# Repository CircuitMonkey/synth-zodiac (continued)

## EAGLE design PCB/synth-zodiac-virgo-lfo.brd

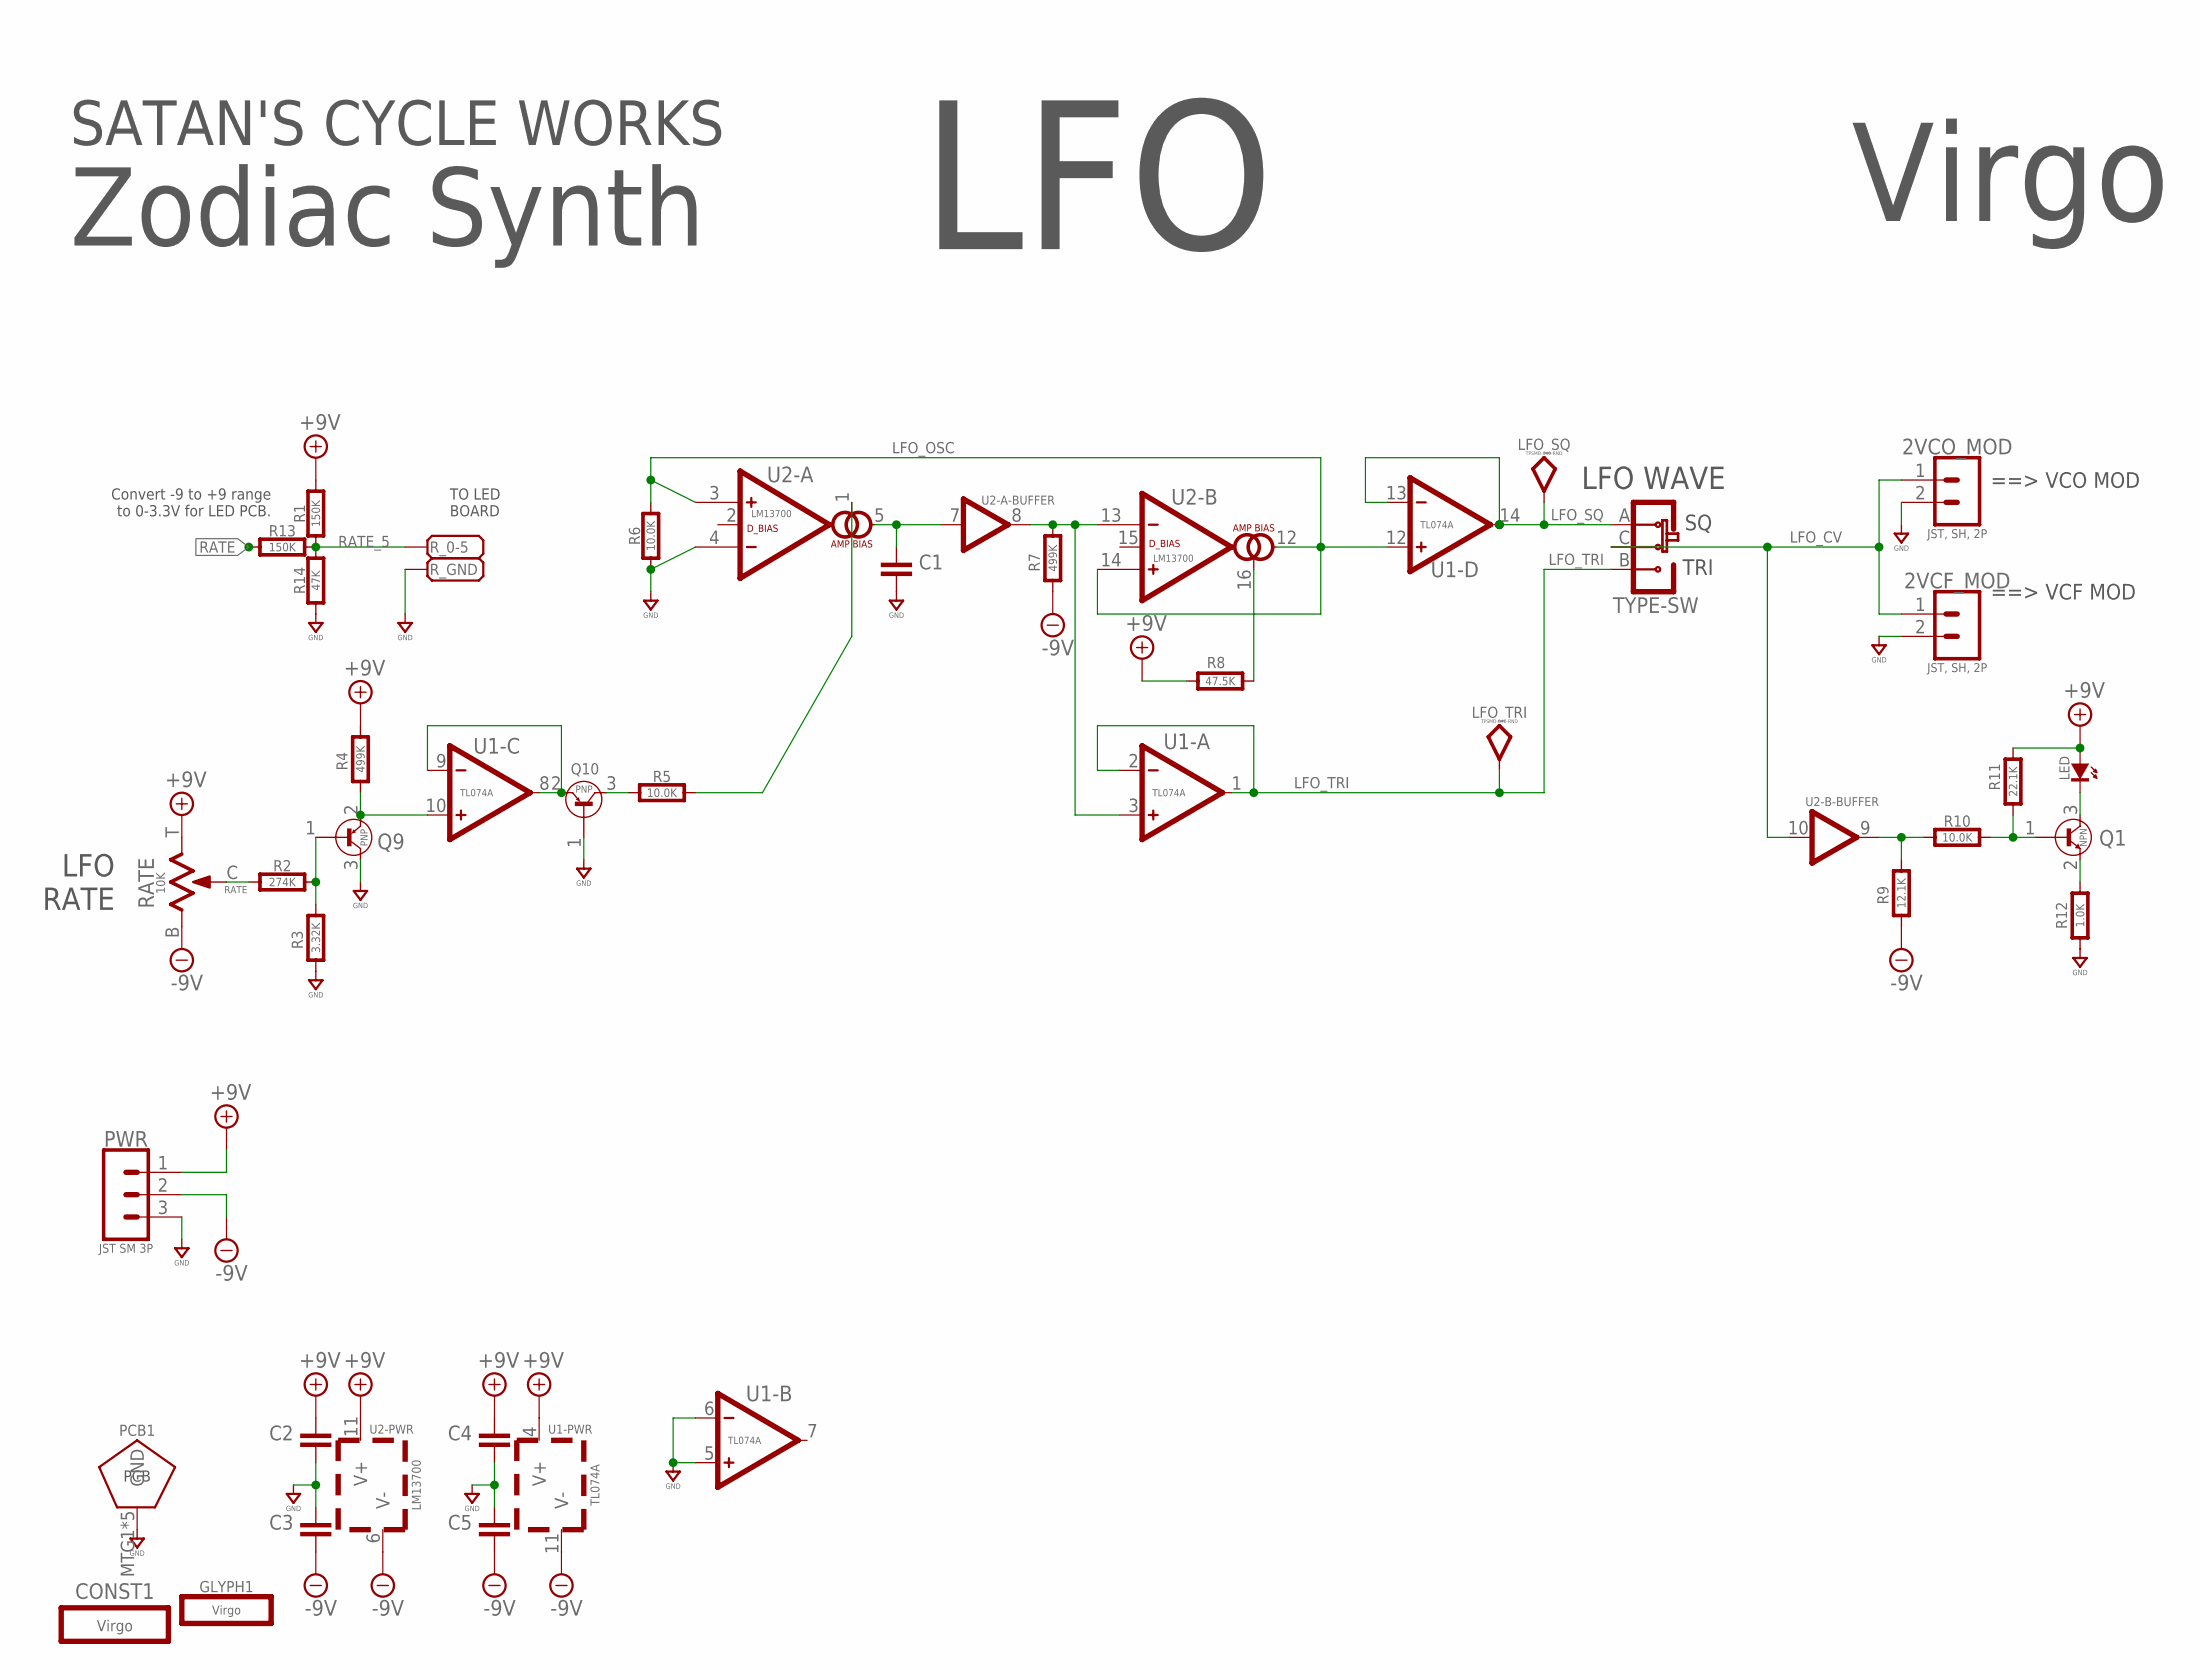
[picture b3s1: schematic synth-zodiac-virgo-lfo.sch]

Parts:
2VCF_MOD, 2VCO_MOD: JST, SH, 2P; BM02B-SRSS-TB
C1, C2, C3, C4, C5: 0.1uF; 0603-CAP
CONST1: Virgo; VIRGO-CONST
GLYPH1: Virgo; VIRGO-GLYPH
LED: BLU; SMD_0603
LFO_SQ: TPSMD-040-RND; SMD-040MIL-RND
LFO_TRI: TPSMD-040-RND; SMD-040MIL-RND
PCB1: PCB FAB; PENTAGON-40MM-RAD
PWR: JST SM 3P; BM03B-SRSS-TB
Q1: NPN; SOT-23
Q9, Q10: PNP; SOT-23
R1, R13: 150K; 0603-RES
R2: 274K; 0603-RES
R3: 3.32K; 0603-RES
R4, R7: 499K; 0603-RES
R5, R6, R10: 10.0K; 0603-RES
R8: 47.5K; 0603-RES
R9: 12.1K; 0603-RES
R11: 22.1K; 0603-RES
R12: 1.0K; 0603-RES
R14: 47K; 0603-RES
RATE: 10K; POT-RV9110
R_0-5: PADSMD-070X070; SMD-070MIL
R_GND: PADSMD-070X070; SMD-070MIL
TYPE: SLIDE-SPDT-MNTSS-12-F45-TH-PCB-2; SS-12-F45-PNL-SMT-2
U1: TL074A; SOP14
U2: LM13700; SO16

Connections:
+9V: C2.1, C4.1, LED.A, PWR.1, R1.2, R4.1, R8.2, R11.1, RATE.T (3), U1.4 (V+), U2.11 (V+)
-9V: C3.2, C5.2, PWR.2, R7.2, R9.2, RATE.B (1), U1.11 (V-), U2.6 (V-)
GND: 2VCF_MOD.2, 2VCO_MOD.2, C1.2, C2.2, C3.1, C4.2, C5.1, PCB1.MTG1, PCB1.MTG2, PCB1.MTG3, PCB1.MTG4, PCB1.MTG5, PWR.3, Q9.3 (COLLECTOR), Q10.1 (BASE), R3.2, R6.1, R12.2, R14.1, R_GND.1, U1.5 (+), U1.6 (-), U2.4 (-)
LFO_CV: 2VCF_MOD.1, 2VCO_MOD.1, TYPE.C, U2.10 (IN)
LFO_OSC: R6.2, U1.12 (+), U2.3 (+), U2.12 (OUT), U2.14 (+)
LFO_SQ: LFO_SQ.TP, TYPE.A, U1.13 (-), U1.14 (OUT)
LFO_TRI: LFO_TRI.TP, TYPE.B, U1.1 (OUT), U1.2 (-)
unnamed: Q9.1 (BASE), R2.2, R3.1
unnamed: Q9.2 (EMITTER), R4.2, U1.10 (+)
unnamed: Q10.2 (EMITTER), U1.8 (OUT), U1.9 (-)
unnamed: Q10.3 (COLLECTOR), R5.1
unnamed: R5.2, U2.1 (AMP-BIAS)
unnamed: C1.1, U2.5 (OUT), U2.7 (IN)
unnamed: R7.1, U1.3 (+), U2.8 (OUT), U2.13 (-)
unnamed: R8.1, U2.16 (AMP-BIAS)
unnamed: Q1.1 (BASE), R10.2, R11.2
unnamed: Q1.2 (EMITTER), R12.1
unnamed: R9.1, R10.1, U2.9 (OUT)
unnamed: LED.K (C), Q1.3 (COLLECTOR)
RATE: R2.1, R13.1, RATE.C (2)
RATE_5: R1.1, R13.2, R14.2, R_0-5.1

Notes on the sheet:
LFO RATE
LFO WAVE
TRI
==> VCO MOD
==> VCF MOD
TO LED BOARD
Convert -9 to +9 range to 0-3.3V for LED PCB.
LFO
Zodiac Synth
Virgo
SATAN'S CYCLE WORKS

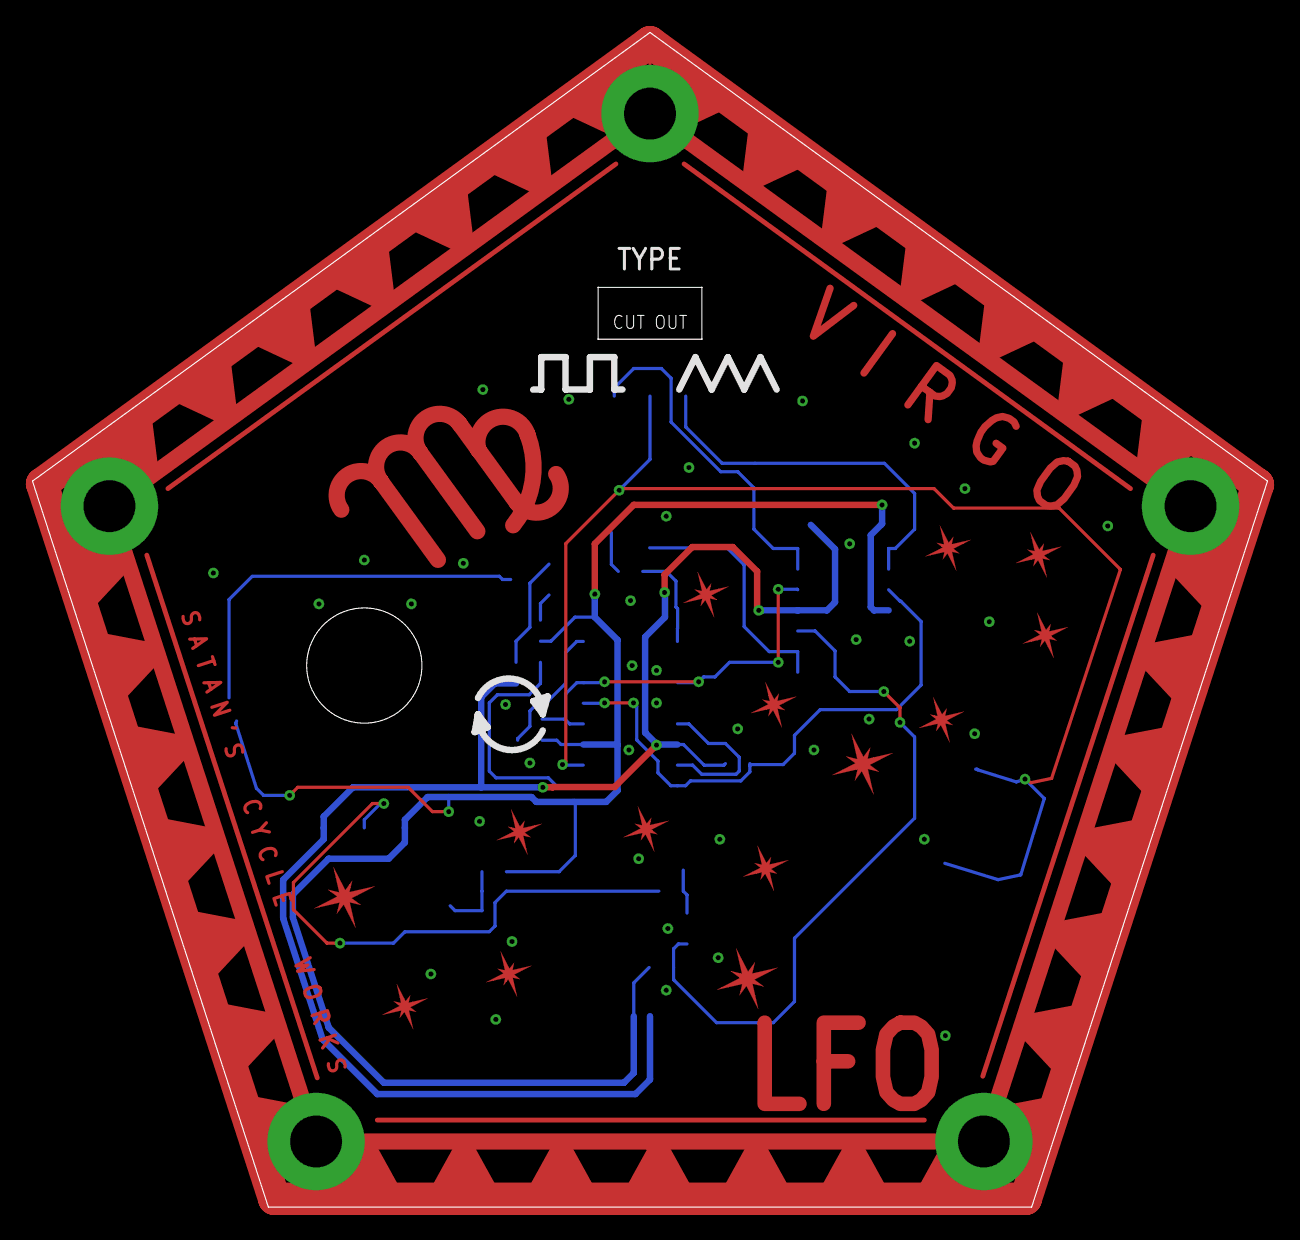
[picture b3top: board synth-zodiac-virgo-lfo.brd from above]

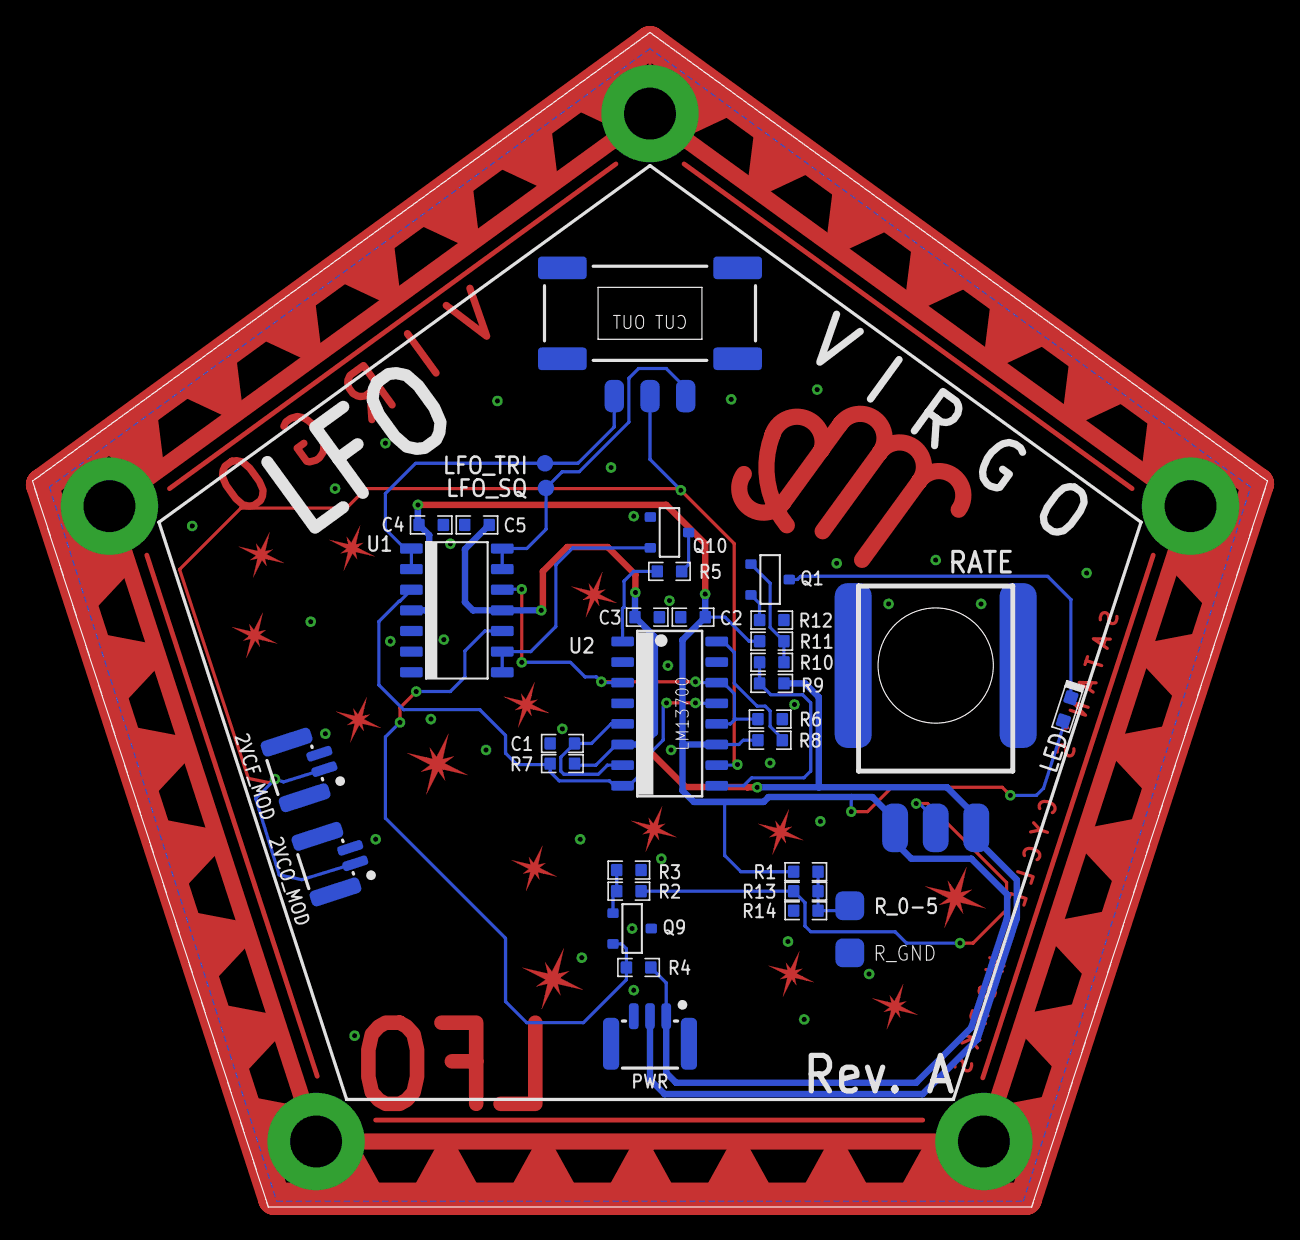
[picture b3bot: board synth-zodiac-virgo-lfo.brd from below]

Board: 2 copper layers, 76.1 x 72.3 mm, 37 parts (33 on the bottom side), 21 nets.

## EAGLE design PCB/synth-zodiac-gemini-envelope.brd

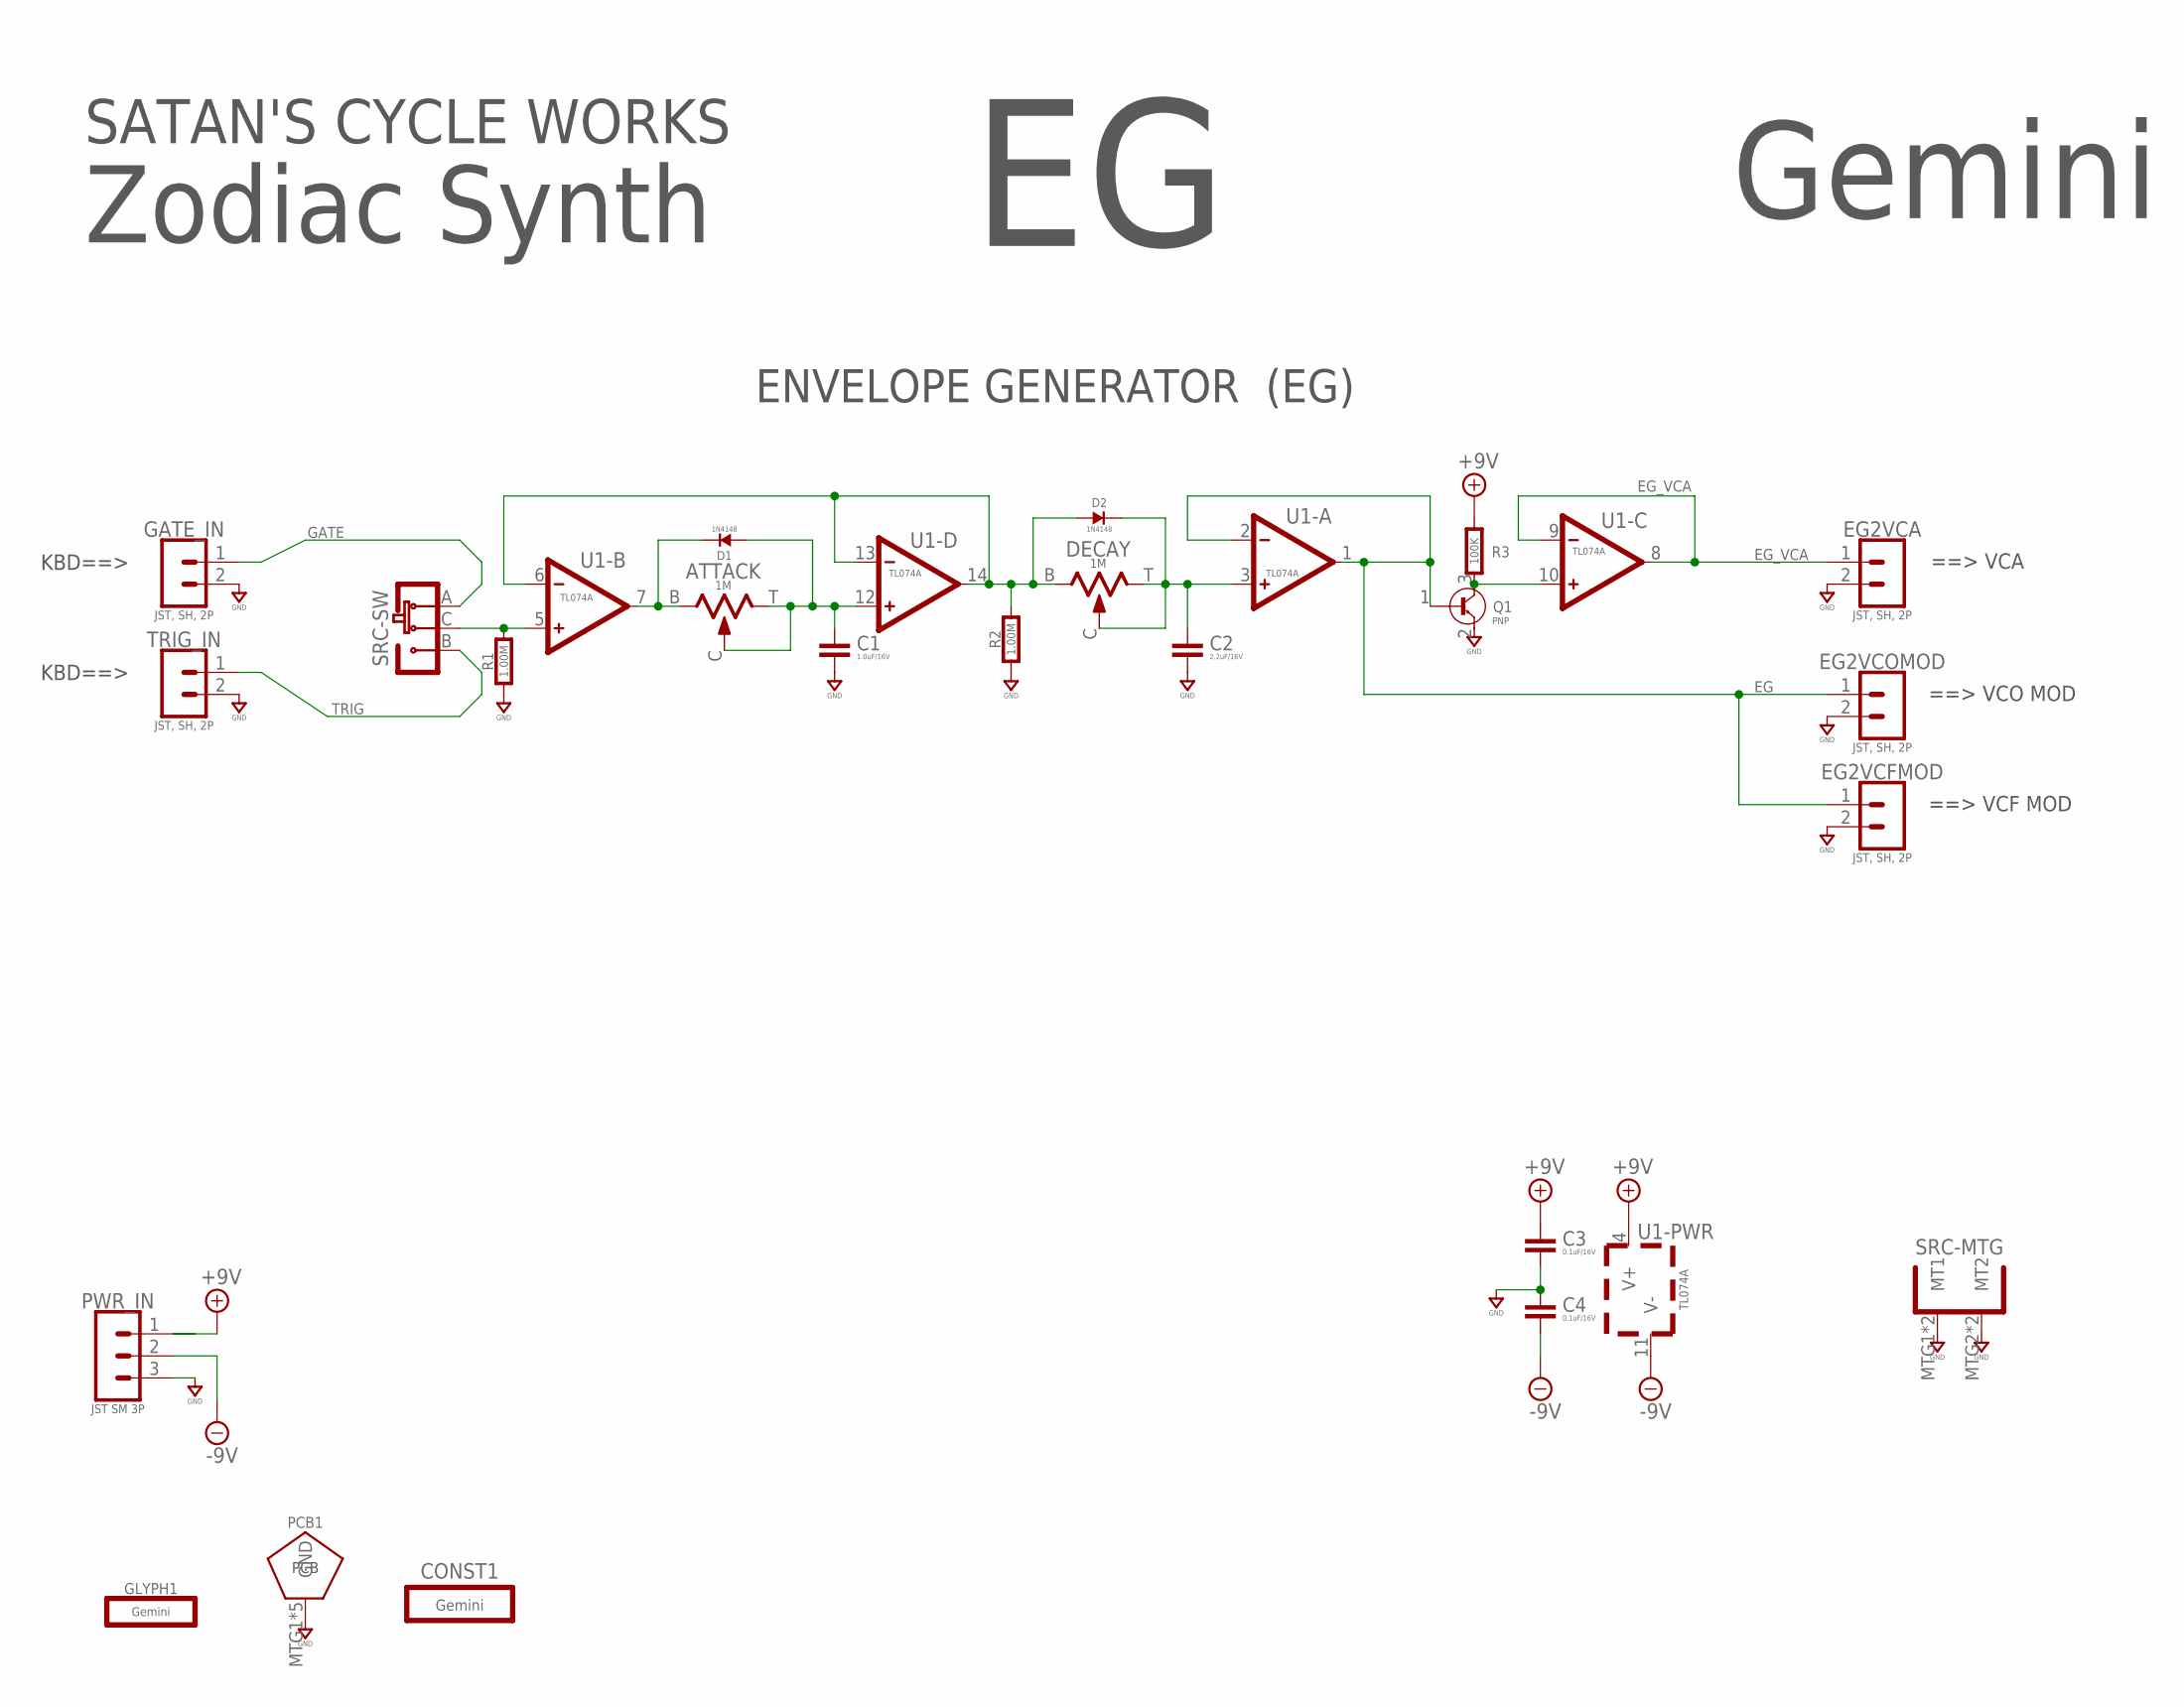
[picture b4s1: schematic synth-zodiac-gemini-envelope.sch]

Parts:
ATTACK: 1M; POT-RV9110
C1: 1.0uF/16V; 0603-CAP
C2: 2.2uF/16V; 0603-CAP
C3, C4: 0.1uF/16V; 0603-CAP
CONST1: Gemini; GEMINI-CONST
D1, D2: 1N4148; SOD-123
DECAY: 1M; POT-RV9110
EG2VCA, EG2VCFMOD, EG2VCOMOD: JST, SH, 2P; BM02B-SRSS-TB
GATE_IN: JST, SH, 2P; BM02B-SRSS-TB
GLYPH1: Gemini; GEMINI-GLYPH
PCB1: PCB FAB; PENTAGON-40MM-RAD
PWR_IN: JST SM 3P; BM03B-SRSS-TB
Q1: PNP; SOT-23
R1, R2: 1.00M; 0603-RES
R3: 100K; 0603-RES
SRC: SLIDE-SPDT-MNTSS-12-F45-TH-PCB-2; SS-12-F45-PNL-SMT-2
TRIG_IN: JST, SH, 2P; BM02B-SRSS-TB
U1: TL074A; SOP14

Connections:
+9V: C3.1, PWR_IN.1, R3.2, U1.4 (V+)
-9V: C4.2, PWR_IN.2, U1.11 (V-)
EG: EG2VCFMOD.1, EG2VCOMOD.1, Q1.1 (BASE), U1.1 (OUT), U1.2 (-)
EG_VCA: EG2VCA.1, U1.8 (OUT), U1.9 (-)
GATE: GATE_IN.1, SRC.A
GND: C1.2, C2.2, C3.2, C4.1, EG2VCA.2, EG2VCFMOD.2, EG2VCOMOD.2, GATE_IN.2, PCB1.MTG1, PCB1.MTG2, PCB1.MTG3, PCB1.MTG4, PCB1.MTG5, PWR_IN.3, Q1.2 (EMITTER), R1.1, R2.1, SRC.MTG1 (MT1), SRC.MTG2 (MT2), SRC.MTG3 (MT1), SRC.MTG4 (MT2), TRIG_IN.2
unnamed: R1.2, SRC.C, U1.5 (+)
unnamed: ATTACK.B (1), D1.K, U1.7 (OUT)
unnamed: ATTACK.C (2), ATTACK.T (3), C1.1, D1.A, U1.12 (+)
unnamed: C2.1, D2.K, DECAY.C (2), DECAY.T (3), U1.3 (+)
unnamed: D2.A, DECAY.B (1), R2.2, U1.6 (-), U1.13 (-), U1.14 (OUT)
unnamed: Q1.3 (COLLECTOR), R3.1, U1.10 (+)
TRIG: SRC.B, TRIG_IN.1

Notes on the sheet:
ENVELOPE GENERATOR (EG)
==> VCO MOD
==> VCA
==> VCF MOD
KBD==>
Zodiac Synth
Gemini
SATAN'S CYCLE WORKS

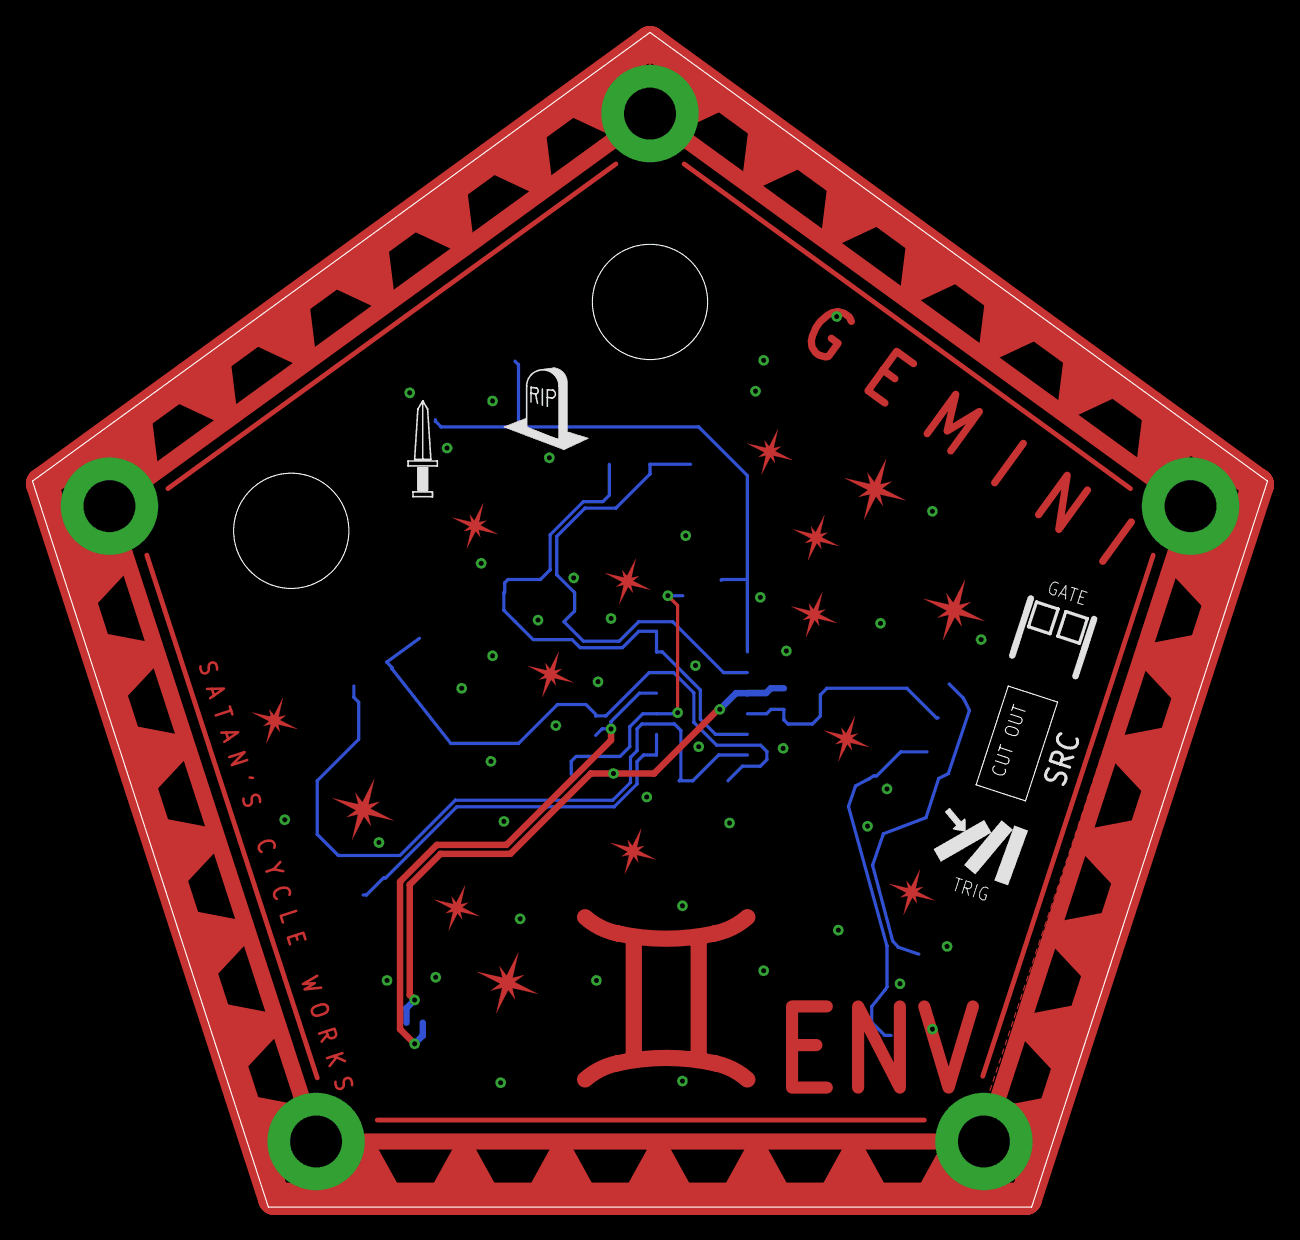
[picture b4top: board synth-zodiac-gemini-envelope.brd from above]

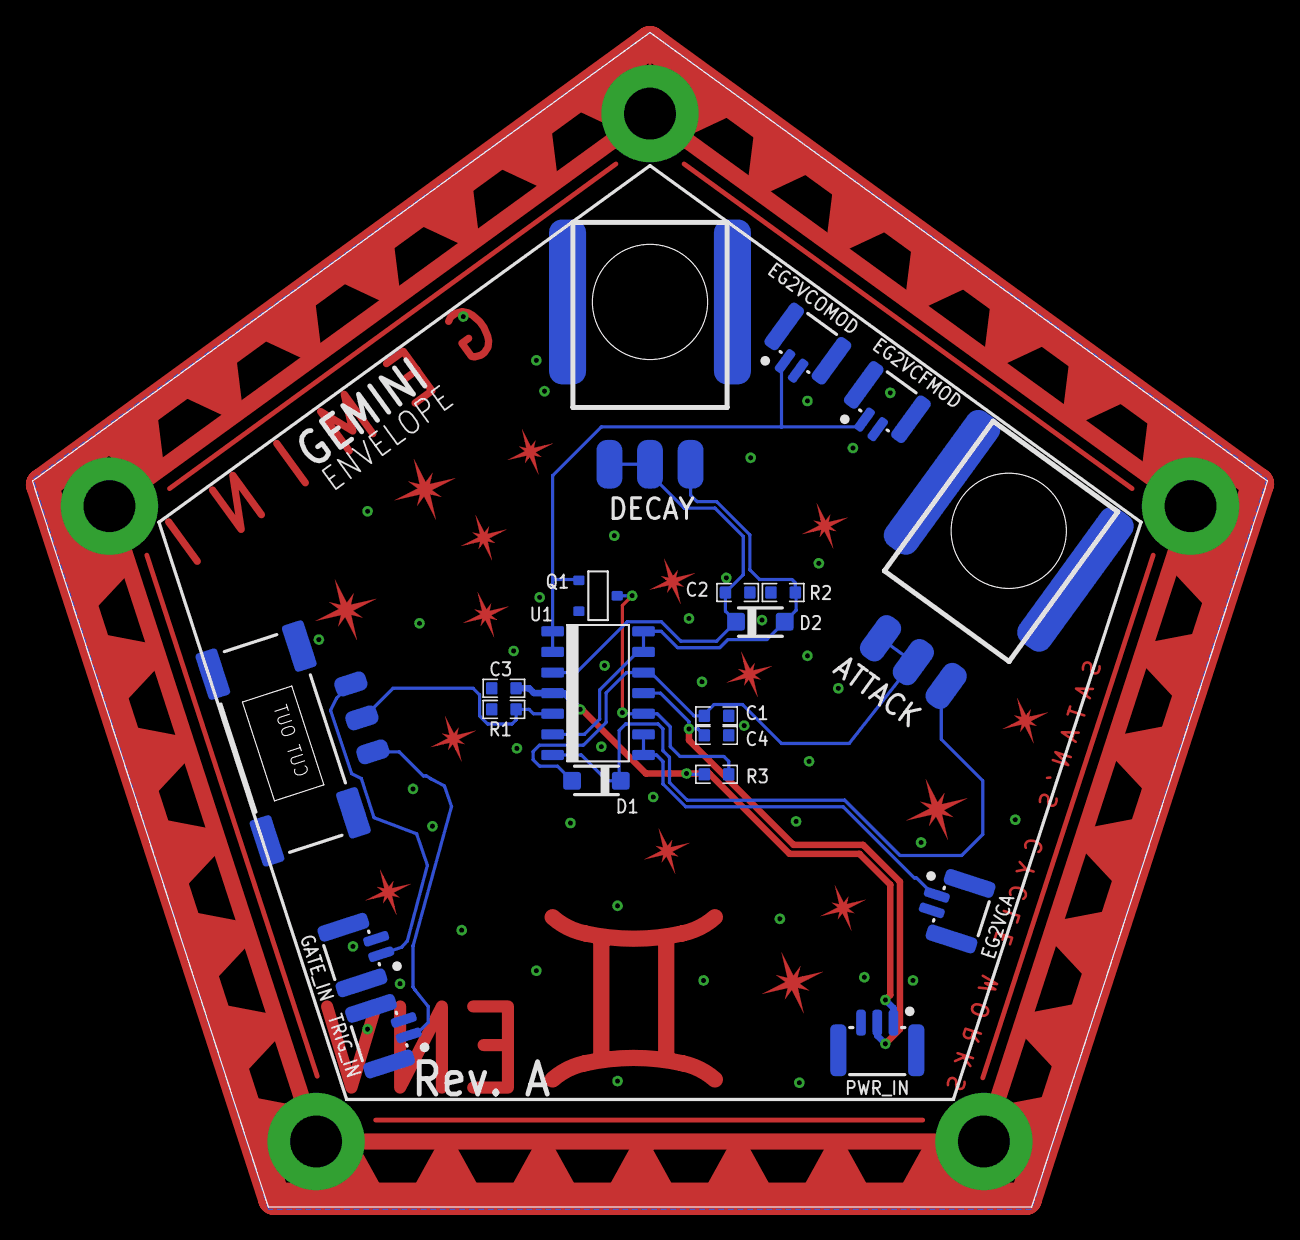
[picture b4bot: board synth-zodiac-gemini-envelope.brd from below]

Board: 2 copper layers, 76.1 x 72.3 mm, 23 parts (19 on the bottom side), 13 nets.
